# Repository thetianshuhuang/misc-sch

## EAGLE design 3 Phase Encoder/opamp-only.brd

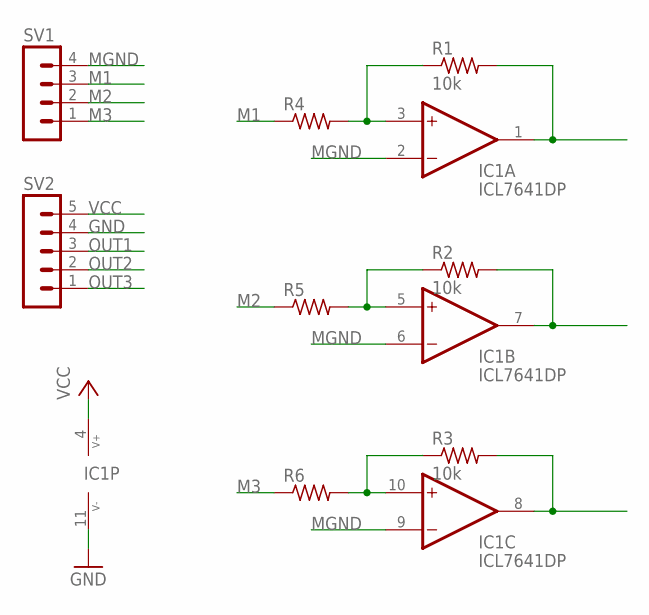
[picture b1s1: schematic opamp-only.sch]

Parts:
IC1: ICL7641DP; DIL14
R1, R2, R3: 10k; 0207/7
R4, R5, R6: R-US_0207/7; 0207/7
SV1: MA04-1
SV2: MA05-1

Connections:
GND: IC1.11 (V-), SV2.4
I1: IC1.3 (+IN), R1.1, R4.2
I2: IC1.5 (+IN), R2.1, R5.2
I3: IC1.10 (+IN), R3.1, R6.2
M1: R4.1, SV1.3
M2: R5.1, SV1.2
M3: R6.1, SV1.1
MGND: IC1.2 (-IN), IC1.6 (-IN), IC1.9 (-IN), SV1.4
OUT1: IC1.1 (OUT), R1.2, SV2.3
OUT2: IC1.7 (OUT), R2.2, SV2.2
OUT3: IC1.8 (OUT), R3.2, SV2.1
VCC: IC1.4 (V+), SV2.5

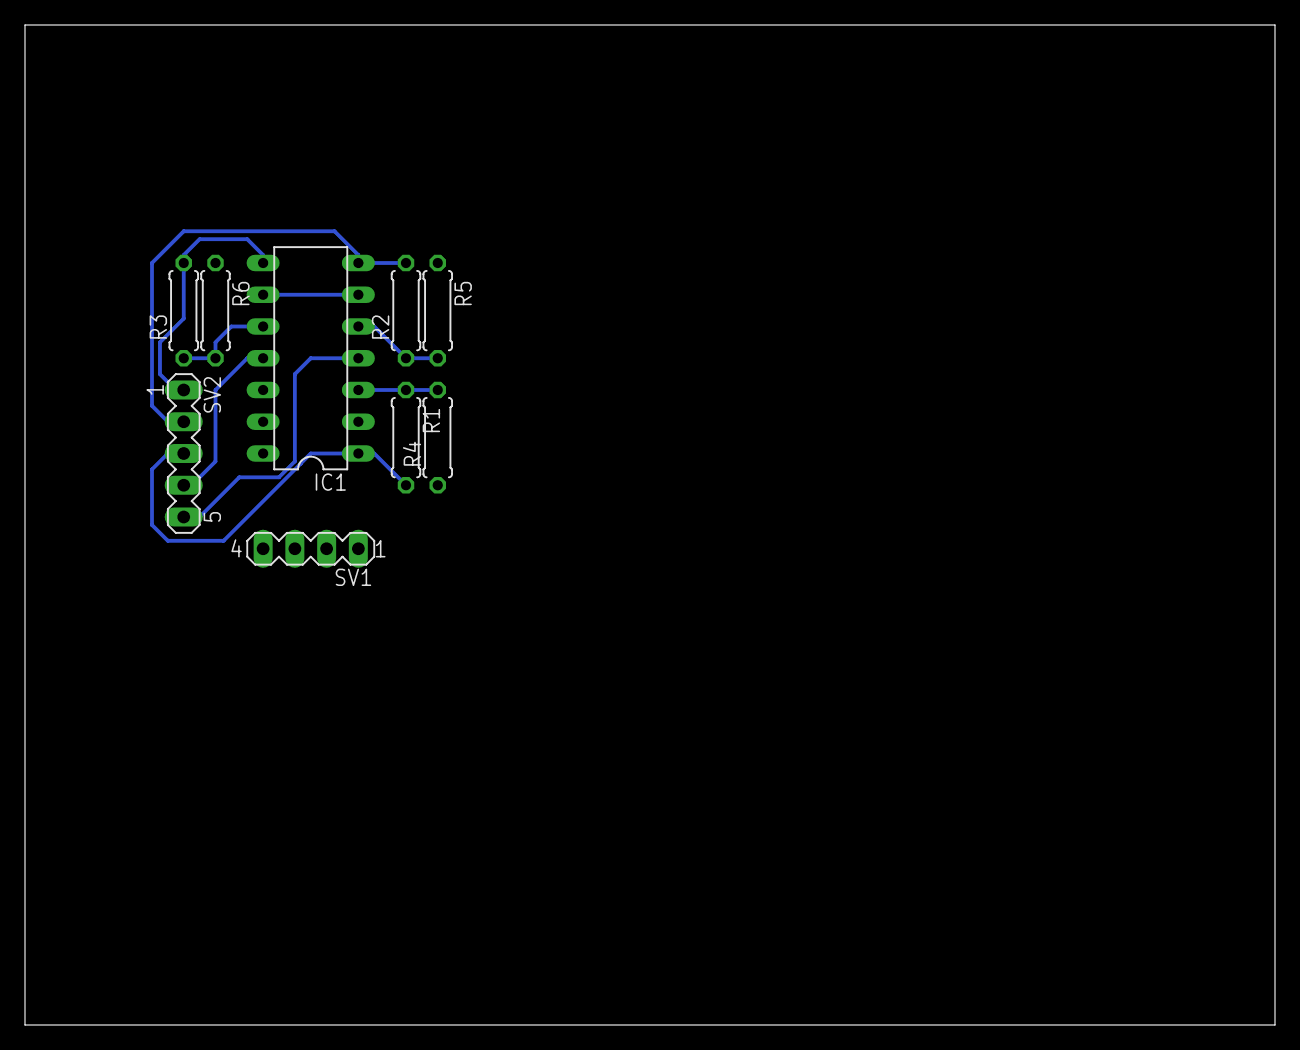
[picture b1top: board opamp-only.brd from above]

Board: 2 copper layers, 100.0 x 80.0 mm, 9 parts (0 on the bottom side), 12 nets.

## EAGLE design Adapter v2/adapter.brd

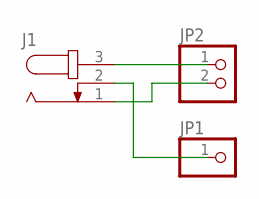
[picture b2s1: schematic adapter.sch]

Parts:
J1: JACK-PLUG0; SPC4077
JP1: PINHD-1X1; 1X01
JP2: PINHD-1X2; 1X02

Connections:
unnamed: J1.3, JP2.1
unnamed: J1.1, JP2.2
unnamed: J1.2, JP1.1

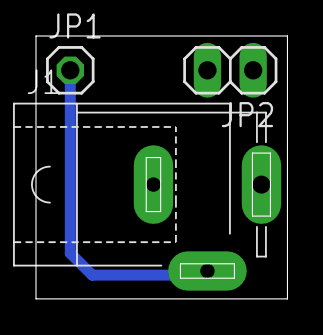
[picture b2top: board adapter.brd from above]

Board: 2 copper layers, 14.0 x 14.6 mm, 3 parts (0 on the bottom side), 3 nets.

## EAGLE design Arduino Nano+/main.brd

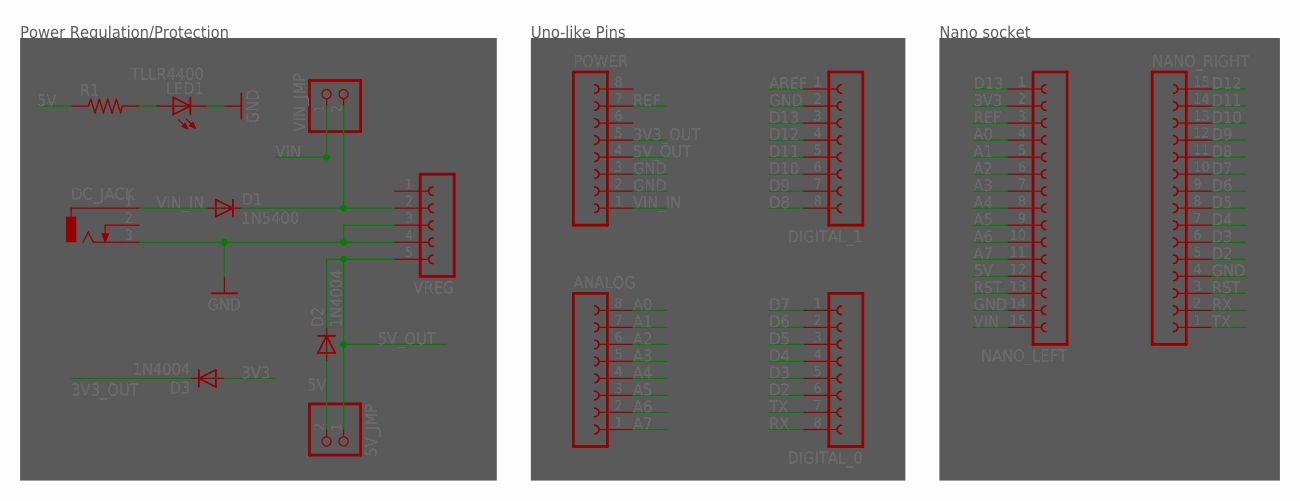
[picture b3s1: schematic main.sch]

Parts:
5V_JMP: PINHD-1X2; 1X02
ANALOG: FE08-1; FE08
D1: 1N5400; DO201-15
D2, D3: 1N4004; DO41-10
DC_JACK: DCJ0303
DIGITAL_0, DIGITAL_1: FE08-1; FE08
LED1: TLLR4400; LED3MM
NANO_LEFT: FE15-1; FE15
NANO_RIGHT: FE15-1; FE15
POWER: FE08-1; FE08
R1: R-US_0207/10; 0207/10
VIN_JMP: PINHD-1X2; 1X02
VREG: FE05-1

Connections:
3V3: D3.A, NANO_LEFT.2
3V3_OUT: D3.C, POWER.5
5V: 5V_JMP.2, D2.A, NANO_LEFT.12, R1.1
5V_OUT: 5V_JMP.1, D2.C, POWER.4, VREG.5
A0: ANALOG.8, NANO_LEFT.4
A1: ANALOG.7, NANO_LEFT.5
A2: ANALOG.6, NANO_LEFT.6
A3: ANALOG.5, NANO_LEFT.7
A4: ANALOG.4, NANO_LEFT.8
A5: ANALOG.3, NANO_LEFT.9
A6: ANALOG.2, NANO_LEFT.10
A7: ANALOG.1, NANO_LEFT.11
AREF: DIGITAL_1.1
D2: DIGITAL_0.6, NANO_RIGHT.5
D3: DIGITAL_0.5, NANO_RIGHT.6
D4: DIGITAL_0.4, NANO_RIGHT.7
D5: DIGITAL_0.3, NANO_RIGHT.8
D6: DIGITAL_0.2, NANO_RIGHT.9
D7: DIGITAL_0.1, NANO_RIGHT.10
D8: DIGITAL_1.8, NANO_RIGHT.11
D9: DIGITAL_1.7, NANO_RIGHT.12
D10: DIGITAL_1.6, NANO_RIGHT.13
D11: DIGITAL_1.5, NANO_RIGHT.14
D12: DIGITAL_1.4, NANO_RIGHT.15
D13: DIGITAL_1.3, NANO_LEFT.1
GND: DC_JACK.3, DIGITAL_1.2, LED1.K (C), NANO_LEFT.14, NANO_RIGHT.4, POWER.2, POWER.3, VREG.3, VREG.4
unnamed: LED1.A, R1.2
unnamed: D1.C, VIN_JMP.2, VREG.2
REF: NANO_LEFT.3, POWER.7
RST: NANO_LEFT.13, NANO_RIGHT.3
RX: DIGITAL_0.8, NANO_RIGHT.2
TX: DIGITAL_0.7, NANO_RIGHT.1
VIN: NANO_LEFT.15, VIN_JMP.1
VIN_IN: D1.A, DC_JACK.1, POWER.1

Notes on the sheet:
Power Regulation/Protection
Uno-like Pins
Nano socket

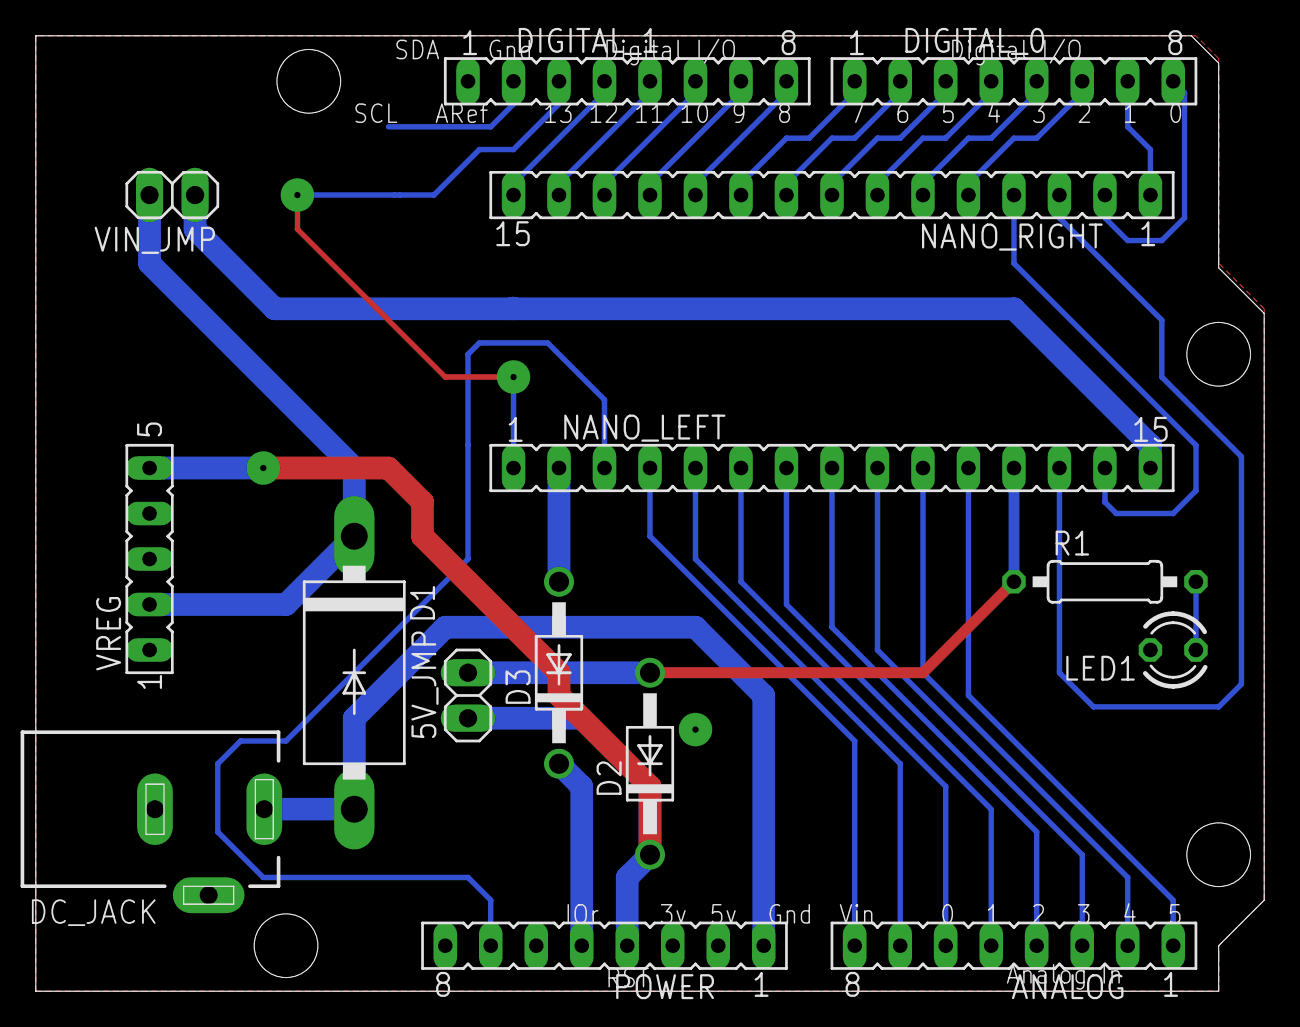
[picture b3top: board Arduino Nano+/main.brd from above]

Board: 2 copper layers, 68.6 x 53.3 mm, 15 parts (0 on the bottom side), 33 nets.

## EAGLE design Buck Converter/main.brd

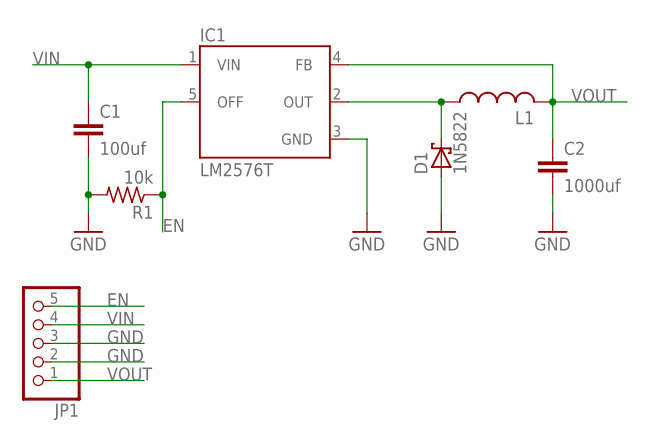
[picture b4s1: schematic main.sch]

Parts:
C1: 100uf; C050-075X075
C2: 1000uf; C050-075X075
D1: 1N5822; CB417-15
IC1: LM2576T; TO220-5
JP1: PINHD-1X5/90; 1X05/90
L1: L-USTJ3-U1; TJ3-U1
R1: 10k; 0207/7

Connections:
EN: IC1.5 (OFF), JP1.5, R1.1
GND: C1.2, C2.2, D1.A, IC1.3 (GND), JP1.2, JP1.3, R1.2
unnamed: D1.C, IC1.2 (OUT), L1.1
VIN: C1.1, IC1.1 (VIN), JP1.4
VOUT: C2.1, IC1.4 (FB), JP1.1, L1.2

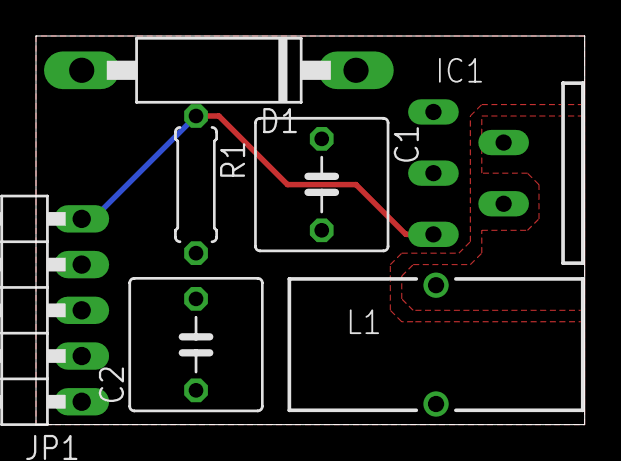
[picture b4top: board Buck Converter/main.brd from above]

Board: 2 copper layers, 30.5 x 21.6 mm, 7 parts (0 on the bottom side), 5 nets.

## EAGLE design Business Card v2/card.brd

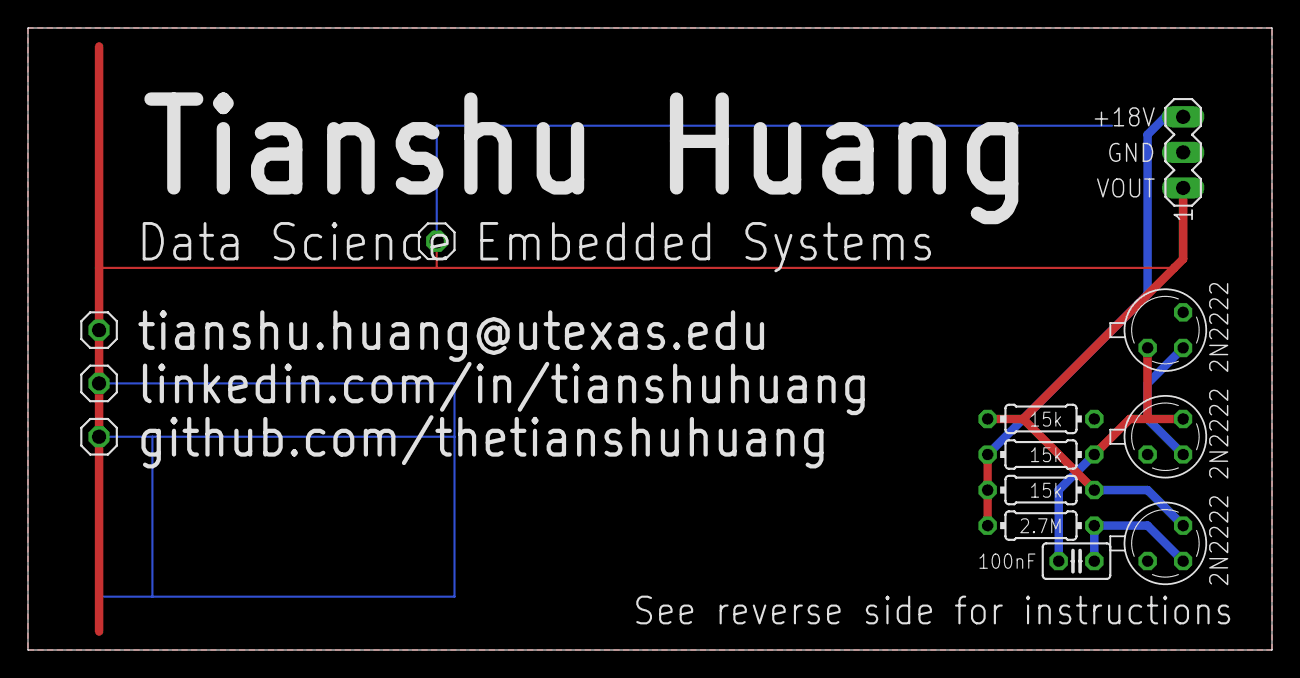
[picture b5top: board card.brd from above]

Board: 2 copper layers, 88.9 x 44.5 mm, 13 parts (0 on the bottom side), 6 nets.

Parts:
C1: 100nF; C025-025X050
JP1, JP2, JP3, JP4: 1X01
R1, R3, R4: 15k; 0204/7
R2: 2.7M; 0204/7
SV1: MA03-1
T1, T2, T3: 2N2222; TO18

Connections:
GND: R4.1, SV1.2, T1.1, T3.1
unnamed: T1.2, T2.2
unnamed: C1.1, R1.1, T1.3, T2.1
unnamed: C1.2, R2.1, T3.2
VCC: R1.2, R2.2, R3.2, SV1.3
VOUT: JP1.1, JP2.1, JP3.1, JP4.1, R3.1, R4.2, SV1.1, T3.3

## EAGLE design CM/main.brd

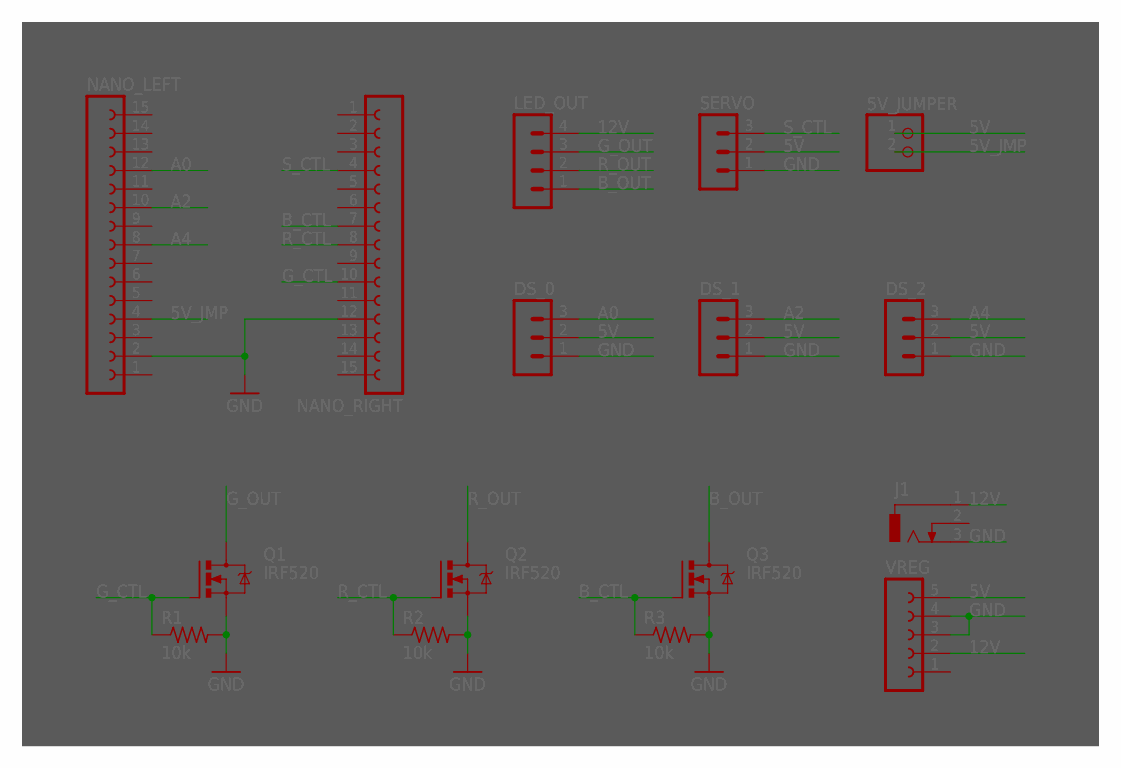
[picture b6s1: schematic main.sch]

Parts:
5V_JUMPER: PINHD-1X2; 1X02
DS_0, DS_1, DS_2: MA03-1
J1: DCJ0303
LED_OUT: MA04-1
NANO_LEFT: FE15-1; FE15
NANO_RIGHT: FE15-1; FE15
Q1, Q2, Q3: IRF520; TO220BV
R1, R2, R3: 10k; 0207/7
SERVO: MA03-1
VREG: FE05W

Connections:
5V: 5V_JUMPER.1, DS_0.2, DS_1.2, DS_2.2, SERVO.2, VREG.5
5V_JMP: 5V_JUMPER.2, NANO_LEFT.4
12V: J1.1, LED_OUT.4, VREG.2
A0: DS_0.3, NANO_LEFT.12
A2: DS_1.3, NANO_LEFT.10
A4: DS_2.3, NANO_LEFT.8
B_CTL: NANO_RIGHT.7, Q3.G, R3.1
B_OUT: LED_OUT.1, Q3.D
GND: DS_0.1, DS_1.1, DS_2.1, J1.3, NANO_LEFT.2, NANO_RIGHT.12, Q1.S, Q2.S, Q3.S, R1.2, R2.2, R3.2, SERVO.1, VREG.3, VREG.4
G_CTL: NANO_RIGHT.10, Q1.G, R1.1
G_OUT: LED_OUT.3, Q1.D
R_CTL: NANO_RIGHT.8, Q2.G, R2.1
R_OUT: LED_OUT.2, Q2.D
S_CTL: NANO_RIGHT.4, SERVO.3

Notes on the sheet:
Arduino Connections
Input/Output
LED Controller
Power

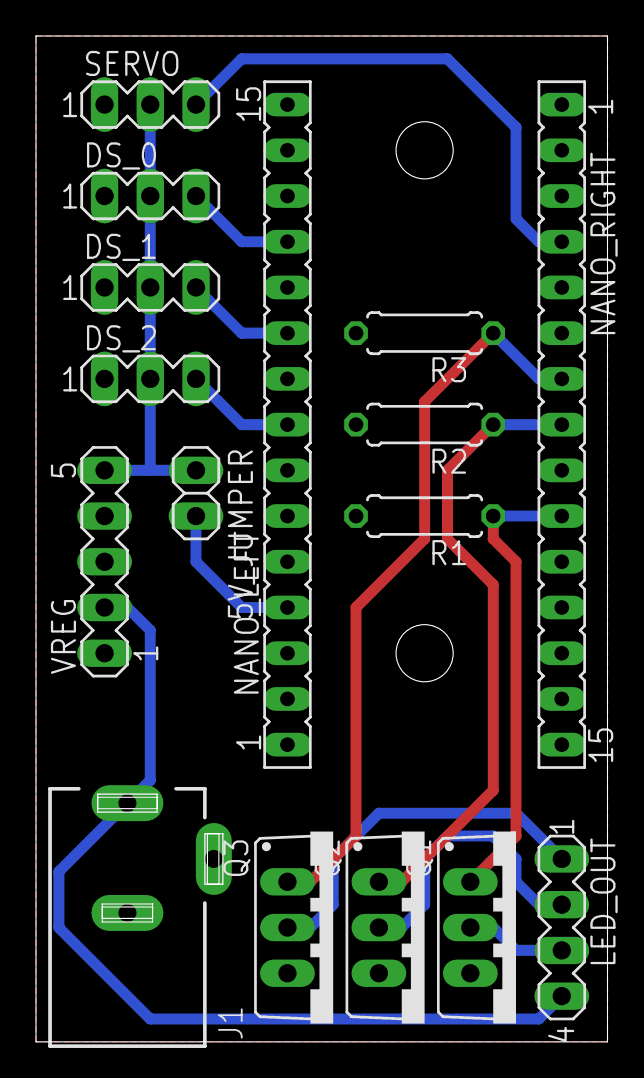
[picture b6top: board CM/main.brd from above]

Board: 2 copper layers, 31.8 x 55.9 mm, 16 parts (0 on the bottom side), 14 nets.
